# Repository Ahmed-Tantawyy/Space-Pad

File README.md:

# Space-Pad
This is an Open-Source code, design, and parts of my macro pad build.

Space-Pad is a customed macro-pad that has 6 shortcut switches, 1 rotary encoder (knob) to mute or change the sound volume, and a screen that displays whatever you want.

General Appearence:

Case from the top:

Case from the bottom:

PCB Design:

Schematic:

PCB in 3D from the top:

PCB in 3D from the bottom:

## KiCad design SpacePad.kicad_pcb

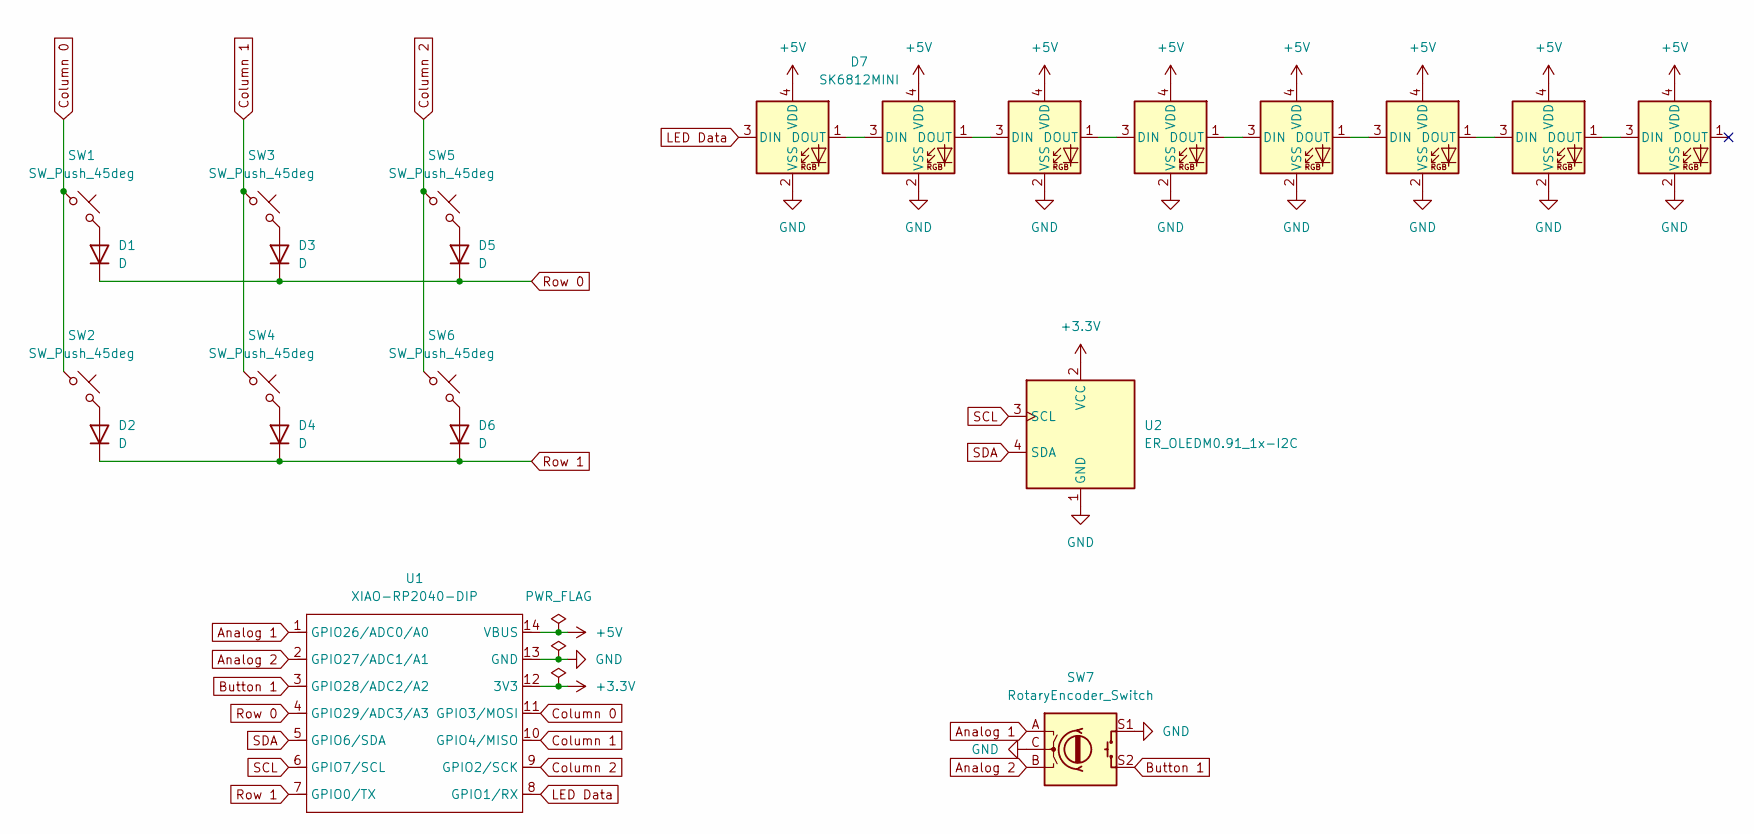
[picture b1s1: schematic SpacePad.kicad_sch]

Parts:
D1, D2, D3, D4, D5, D6: D; D_DO-35_SOD27_P7.62mm_Horizontal
D7, D8, D9, D10, D11, D12, D13, D14: SK6812MINI; LED_SK6812MINI_PLCC4_3.5x3.5mm_P1.75mm
SW1, SW2, SW3, SW4, SW5, SW6: SW_Push_45deg; SW_Cherry_MX_1.00u_PCB
SW7: RotaryEncoder_Switch; RotaryEncoder_Alps_EC11E-Switch_Vertical_H20mm
U1: XIAO-RP2040-DIP; XIAO-Generic-Hybrid-14P-2.54-21X17.8MM
U2: ER_OLEDM0.91_1x-I2C

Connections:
+3.3V: U1.12 (3V3), U2.2 (VCC)
+5V: D7.4 (VDD), D8.4 (VDD), D9.4 (VDD), D10.4 (VDD), D11.4 (VDD), D12.4 (VDD), D13.4 (VDD), D14.4 (VDD), U1.14 (VBUS)
Analog 1: SW7.A, U1.1 (GPIO26/ADC0/A0)
Analog 2: SW7.B, U1.2 (GPIO27/ADC1/A1)
Button 1: SW7.S2, U1.3 (GPIO28/ADC2/A2)
Column 0: SW1.1, SW2.1, U1.11 (GPIO3/MOSI)
Column 1: SW3.1, SW4.1, U1.10 (GPIO4/MISO)
Column 2: SW5.1, SW6.1, U1.9 (GPIO2/SCK)
GND: D7.2 (VSS), D8.2 (VSS), D9.2 (VSS), D10.2 (VSS), D11.2 (VSS), D12.2 (VSS), D13.2 (VSS), D14.2 (VSS), SW7.C, SW7.S1, U1.13 (GND), U2.1 (GND)
LED Data: D7.3 (DIN), U1.8 (GPIO1/RX)
unnamed: D1.2 (A), SW1.2
unnamed: D2.2 (A), SW2.2
unnamed: D3.2 (A), SW3.2
unnamed: D4.2 (A), SW4.2
unnamed: D5.2 (A), SW5.2
unnamed: D6.2 (A), SW6.2
unnamed: D7.1 (DOUT), D8.3 (DIN)
unnamed: D8.1 (DOUT), D9.3 (DIN)
unnamed: D9.1 (DOUT), D10.3 (DIN)
unnamed: D10.1 (DOUT), D11.3 (DIN)
unnamed: D11.1 (DOUT), D12.3 (DIN)
unnamed: D12.1 (DOUT), D13.3 (DIN)
unnamed: D13.1 (DOUT), D14.3 (DIN)
Row 0: D1.1 (K), D3.1 (K), D5.1 (K), U1.4 (GPIO29/ADC3/A3)
Row 1: D2.1 (K), D4.1 (K), D6.1 (K), U1.7 (GPIO0/TX)
SCL: U1.6 (GPIO7/SCL), U2.3 (SCL)
SDA: U1.5 (GPIO6/SDA), U2.4 (SDA)

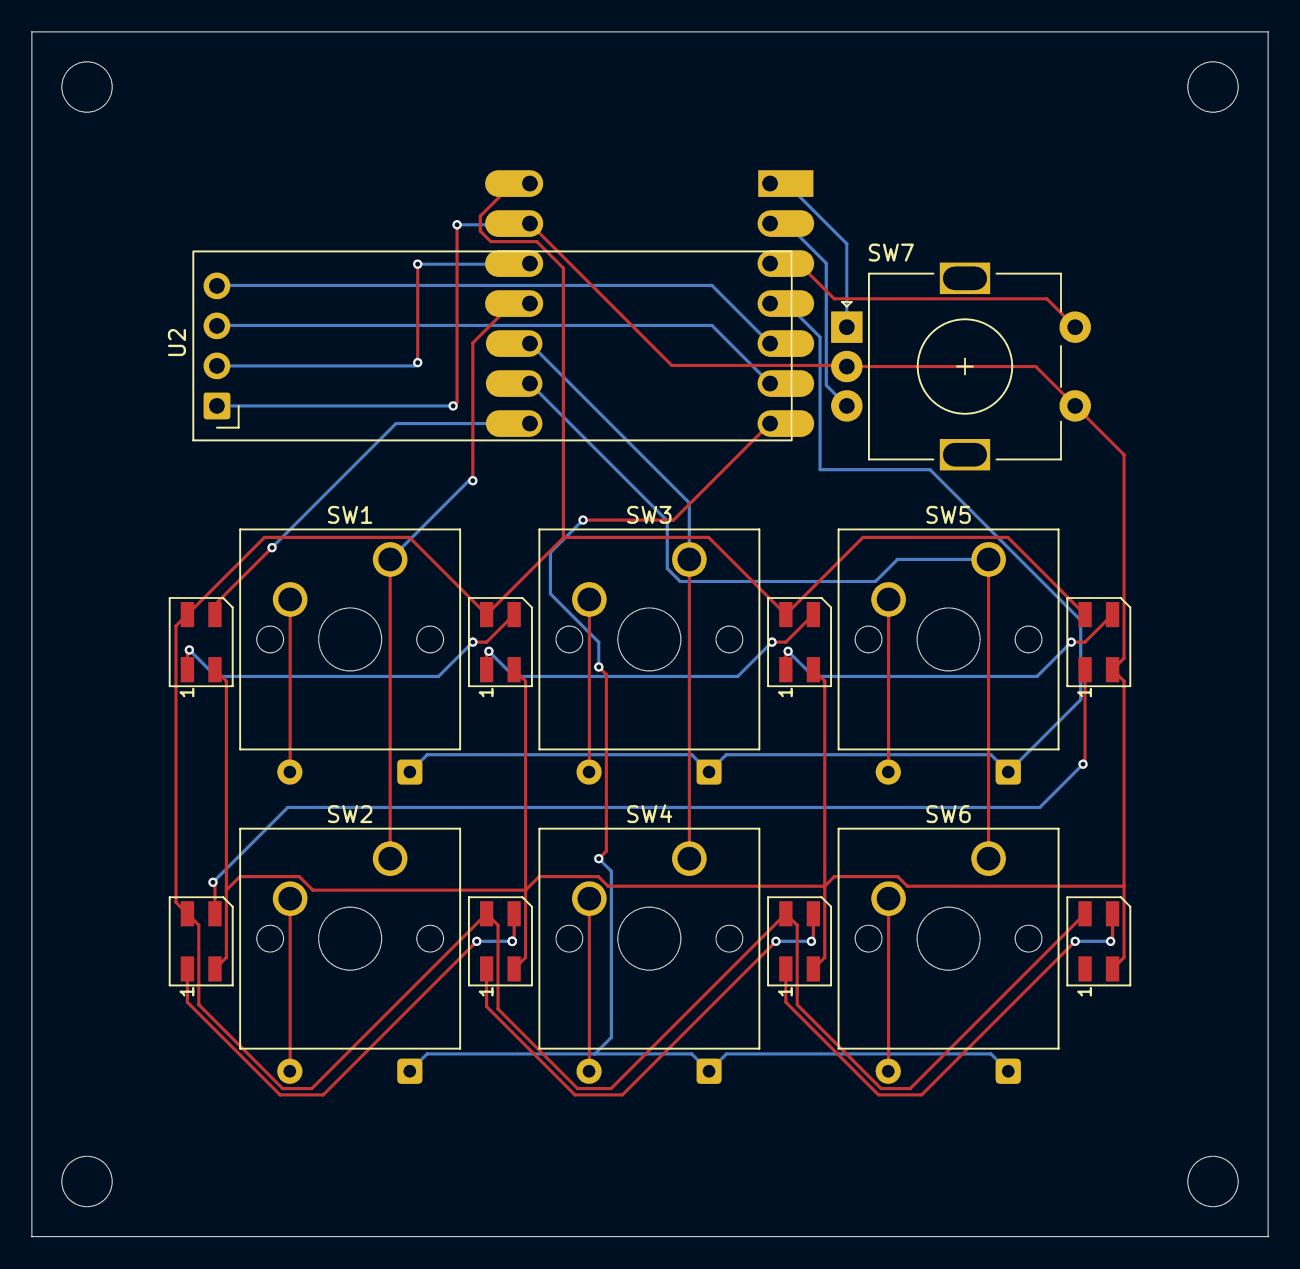
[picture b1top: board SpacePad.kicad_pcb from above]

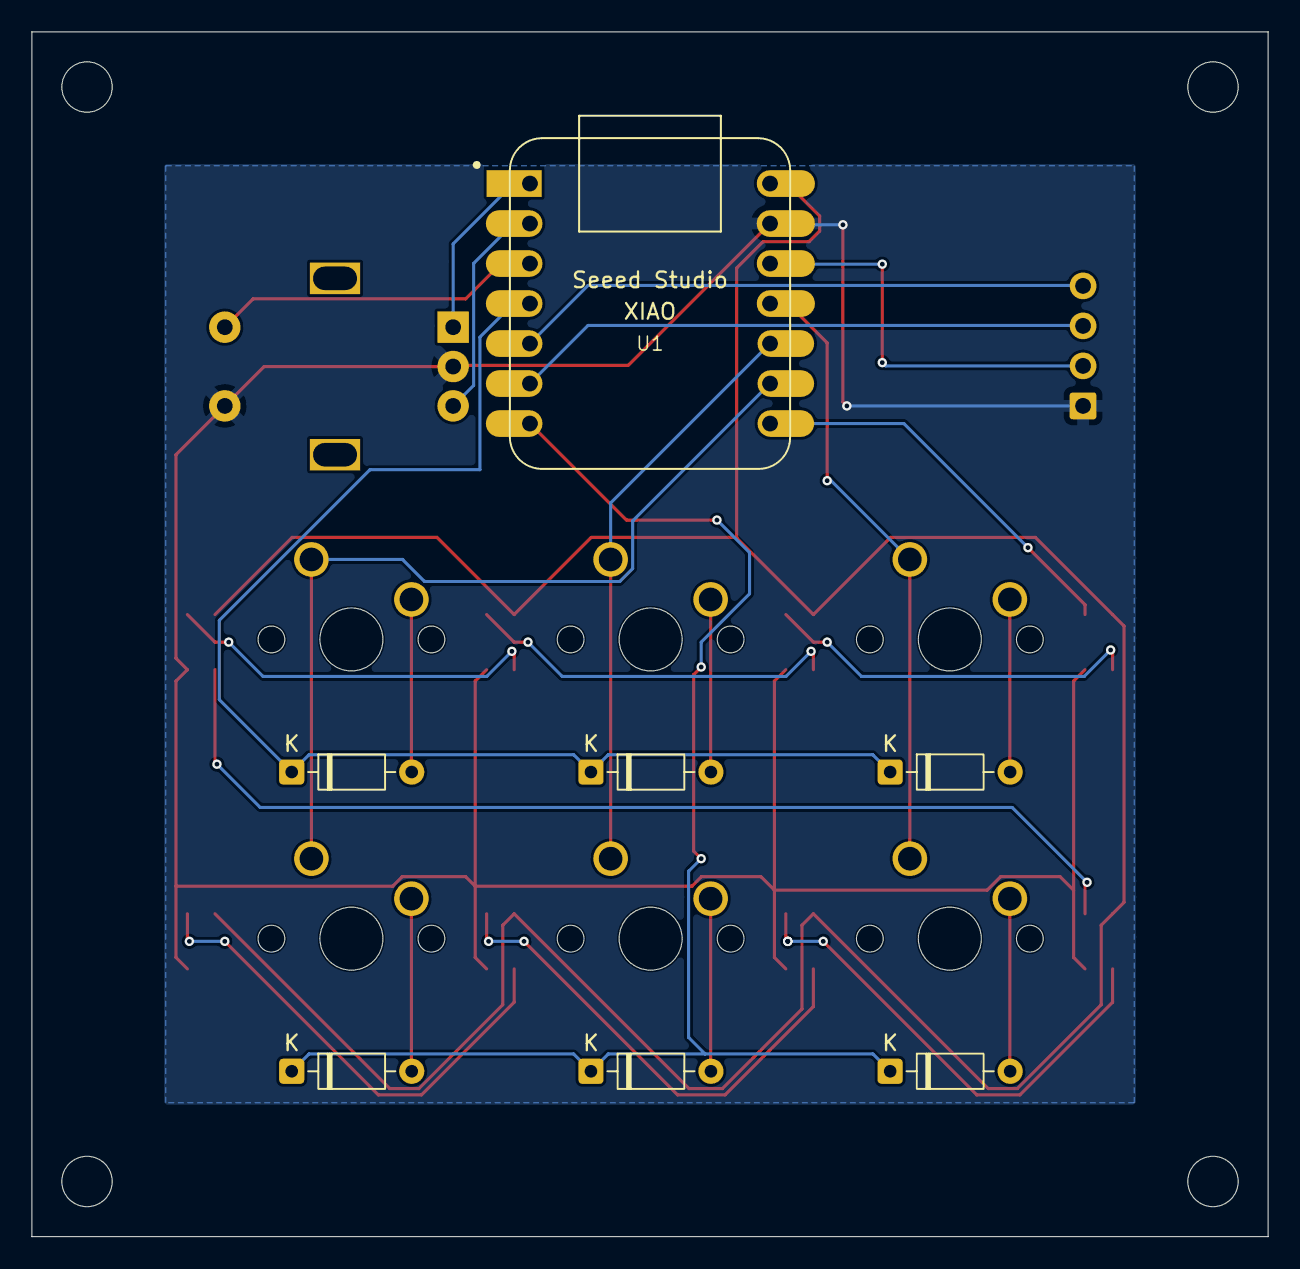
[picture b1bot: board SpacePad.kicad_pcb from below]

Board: 2 copper layers, 78.5 x 76.5 mm, 23 parts (7 on the bottom side), 27 nets.
